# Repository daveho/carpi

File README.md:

Hardware design and code for Raspberry Pi based car entertainment device.  Everything is up and running and works fairly well at this point.  I wrote a [blog post](http://daveho.github.io/2014/04/19/carpi-car-videos-with-the-raspberry-pi.html) that summarizes the project.

The [wiki](https://github.com/daveho/carpi/wiki) has complete information on building the device and installing the software.

Everything (software and hardware) is open source: see the file
LICENSES.txt for details.

The basic idea is being able to play videos and music
from the Raspberry Pi.  The user interface consists
of a 2.2" LCD and 6 keyswitches.  A sandwich-style
enclosure consisting of two pieces of laser-cut acrylic
and various bits of hardware has been designed and assembled.
The "enclosure" directory has complete CAD drawings.

Here is a photo of the assembled device (with the Raspberry Pi,
the LCD module, and the keyswitches):

Current status of the software is

* It's a console (ncurses) app.  This probably won't change,
  although the software makes a clean separation between
  controllers and views, and the former are completely
  independent of the latter, so a proper GUI interface
  could be supported.
* The LCD display is assumed to be 240x320, accessed as
  a Linux framebuffer device with fbcons.  (Specifically,
  an SPI-based LCD using the ILI9340 controller chip,
  supported by fbtft using the "adafruit22a" driver.
  Note that the LCD I'm using isn't specifically the
  Adafruit one, but appears to be completely compatible.)
  With a 8x16 font this gives us a 30x20 text display.
* Music playing works using mpg321 and ogg123 via the
  remote control interface (actually ogg123 playback doesn't
  work, need to investigate this).
* Pushbutton input is supported using the RPi's GPIO.
* Video playing is supported by running omxplayer as a
  subprocess, with video output going to the composite output
  (because composite video monitors for cars are super cheap).

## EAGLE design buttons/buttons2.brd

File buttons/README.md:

This directory has schematics, PCB layout, and firmware for the
board that has the pushbuttons on it.  An attiny2313 or attiny4313
microcontroller does the debouncing.  This board also has a header
that connects to the LCD.

**buttons2.sch** and **buttons2.brd** are the schematic and board layout,
in Eagle CAD.

Rendering (via [OSH Park](http://www.oshpark.com), which is where I had the boards fabricated):

Note that the PCB uses Cherry MX keyboard switches.  **cherrymx.lbr** is a
(very slightly) modified version of the following Eagle library:
https://github.com/c0z3n/cherrymx-eagle

[I sent a pull request with my changes, which were purely improvements
to the schematic symbol.]

**buttons.c** is the firmware that runs on the attiny2313.
**Makefile** will compile it (using avr-gcc) and program it to the
device (using avrdude).

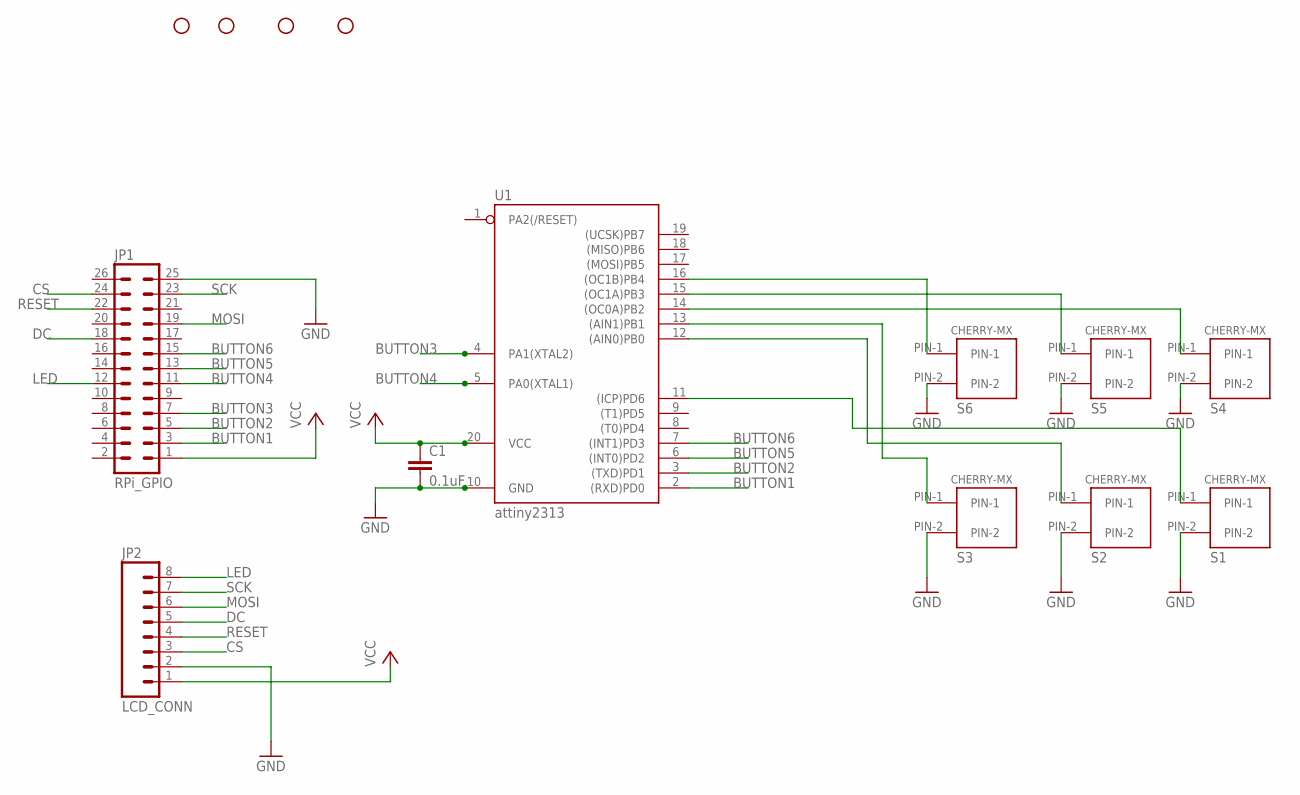
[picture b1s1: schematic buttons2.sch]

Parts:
C1: 0.1uF; C2.5-2
JP1: RPi_GPIO; ML26
JP2: LCD_CONN; 1X08
S1, S2, S3, S4, S5, S6: CHERRY-MX-I
STANDOFF1, STANDOFF2, STANDOFF3, STANDOFF4: STAND-OFF
U1: attiny2313; DIL20

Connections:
BUTTON1: JP1.3, U1.2 ((RXD)PD0)
BUTTON2: JP1.5, U1.3 ((TXD)PD1)
BUTTON3: JP1.7, U1.4 (PA1(XTAL2))
BUTTON4: JP1.11, U1.5 (PA0(XTAL1))
BUTTON5: JP1.13, U1.6 ((INT0)PD2)
BUTTON6: JP1.15, U1.7 ((INT1)PD3)
CS: JP1.24, JP2.3
DC: JP1.18, JP2.5
GND: C1.2, JP1.25, JP2.2, S1.PIN-2, S2.PIN-2, S3.PIN-2, S4.PIN-2, S5.PIN-2, S6.PIN-2, U1.10 (GND)
LED: JP1.12, JP2.8
MOSI: JP1.19, JP2.6
unnamed: S6.PIN-1, U1.16 ((OC1B)PB4)
unnamed: S5.PIN-1, U1.15 ((OC1A)PB3)
unnamed: S4.PIN-1, U1.14 ((OC0A)PB2)
unnamed: S3.PIN-1, U1.13 ((AIN1)PB1)
unnamed: S2.PIN-1, U1.12 ((AIN0)PB0)
unnamed: S1.PIN-1, U1.11 ((ICP)PD6)
RESET: JP1.22, JP2.4
SCK: JP1.23, JP2.7
VCC: C1.1, JP1.1, JP2.1, U1.20 (VCC)

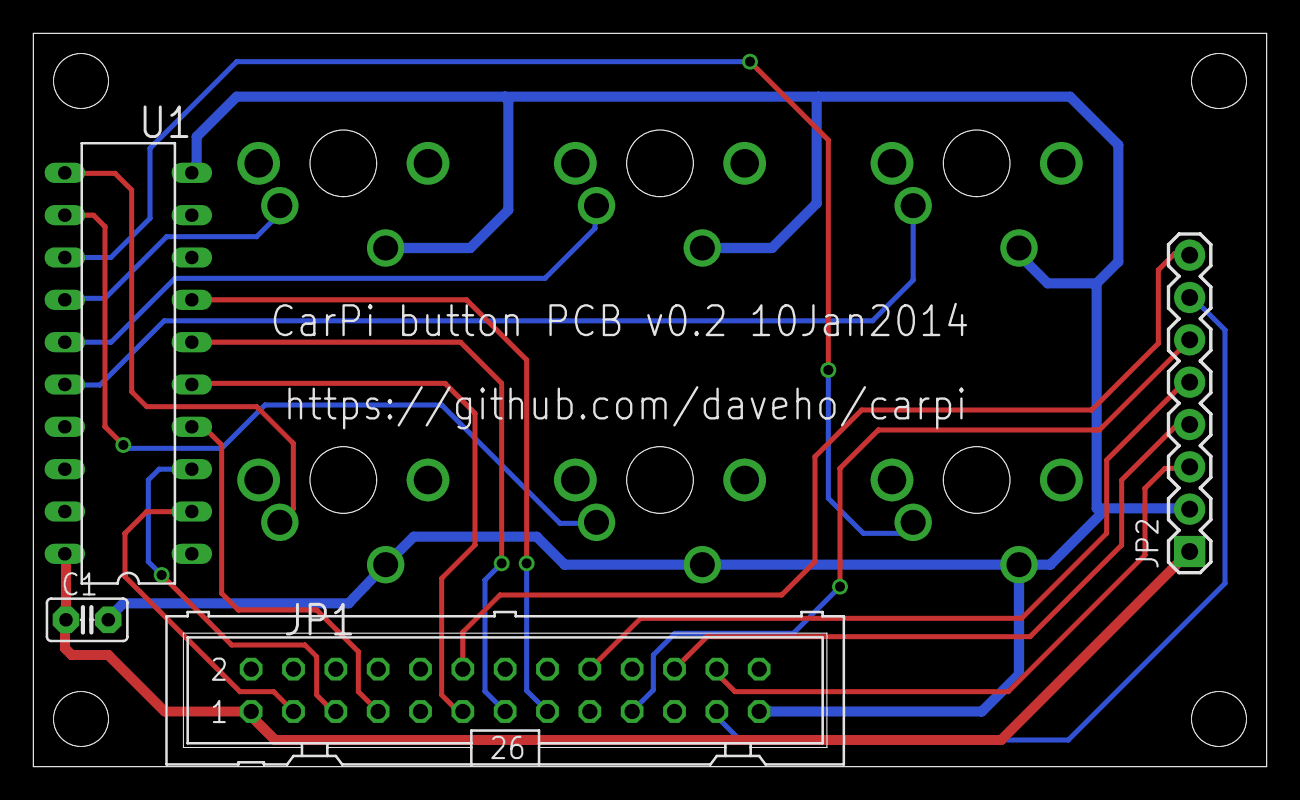
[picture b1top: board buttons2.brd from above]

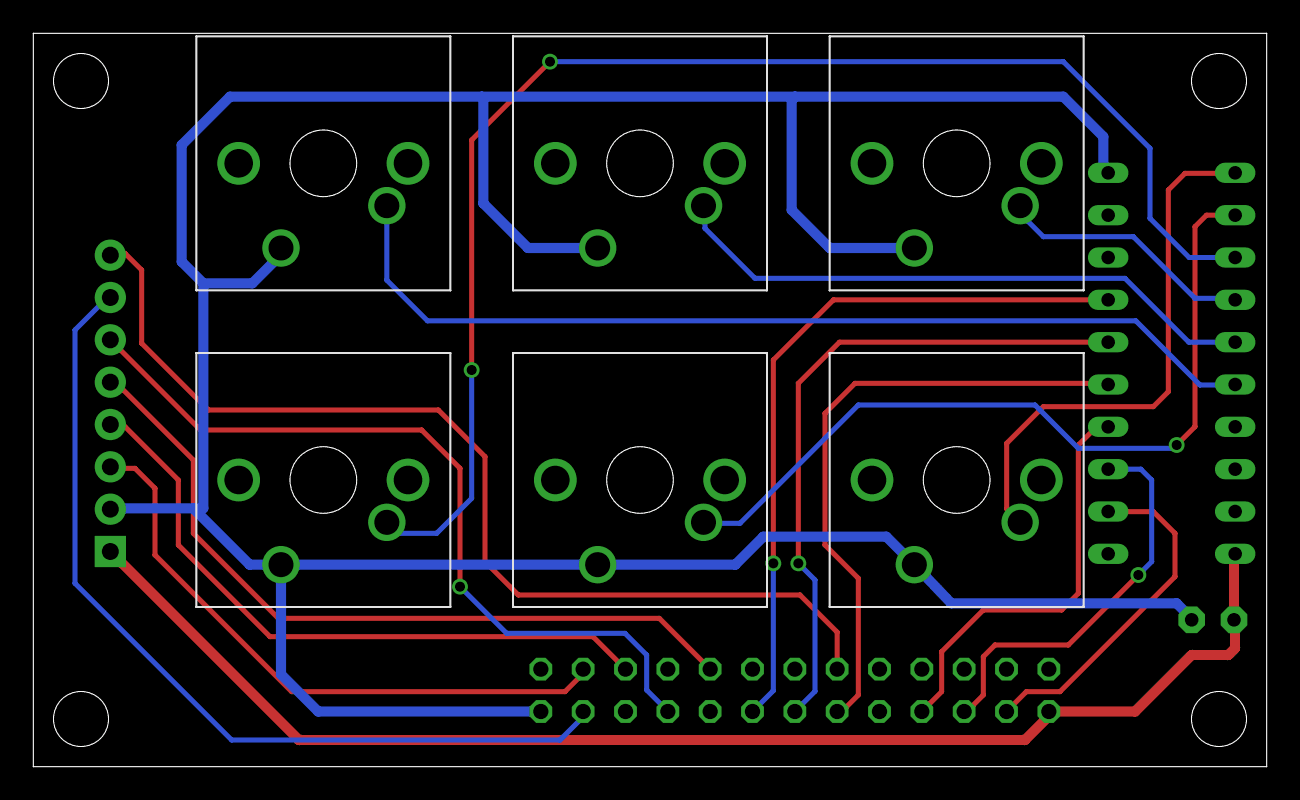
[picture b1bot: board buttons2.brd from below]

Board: 2 copper layers, 74.0 x 44.0 mm, 14 parts (6 on the bottom side), 20 nets.

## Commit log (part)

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2013-12-13 initial checkin of gtk3 tutorial code
2013-12-13 set window width and height
2013-12-13 added CarPiMainWindow object
    This serves as the top-level object for the GUI.
    Contains a GtkFixed as the main container for the
    overall UI.
2013-12-21 started log, enclosure design
2013-12-21 made it 5"x3" to allow room for board mounts
2013-12-21 rpi model B CAD drawing
2013-12-21 notes for 12/21
2013-12-22 new plate size, Rpi outline w/ ref at 0,0
2013-12-22 corrected orientation of Rpi outline
2013-12-22 good progress on enclosure design
2013-12-22 note about fixing orientation of Rpi drawing
2013-12-22 clarification about standoffs
2013-12-23 move standoffs and RPi for better clearance
    Added a layer to the drawing to show the approximate size
    of the standoffs. Was concerned that the bottom right
    standoff would block access to the ethernet port, so moved
    all of the standoffs 1mm horizontally and vertically
    towards the corners, and moved the RPi further towards
    the top. This should allow good clearance for the
2013-12-23 starting drawing of LCD
2013-12-23 basic drawing of LCD
2013-12-23 started parts list
2013-12-23 started outline of buttons protoboard
2013-12-23 more work on parts list
2013-12-23 updates for using 4x6cm board for buttons
2013-12-24 starting over with source code
2013-12-24 restart code, starting with audio player
    Created PlaySound class, for playing an audio file using
    mpg321 or ogg123 using their remote control interface.
    Using CodeLite as the C++ IDE.
2013-12-24 started Thread, Event, and EventQueue classes
    Modified PlaySound to use a Thread subclass for the
    status monitor thread.
2013-12-24 s,Foobar,CarPi,g
2013-12-25 code cleanup
2013-12-25 added MenuController; made ConsMenuView read-only
    From now on, ALL of the views will be read-only, and
    this will be enforced through having model object pointer
    be to a const object.
    This should work really well: since we have our
    own event system, the views have no obligation to
    handle user input events, and in fact do not even
2013-12-25 start support for menu scrolling
2013-12-25 scrolling works!
2013-12-26 started main menu
    There will be one menu class and one menu controller class
    per menu. Seems to be workable. The controller will
    "own" the menu, and thus be responsible for cleaning it
    up when the controller and view are no longer needed.
2013-12-26 made Menu abstract; added StaticMenu
2013-12-26 created CarPiApp main class; started file nav
2013-12-26 set MenuItem ptr in SELECTION_CHANGED events
2013-12-26 directory navigation mostly works!
2013-12-26 only include .mp3 and .ogg files in music nav
2013-12-26 added left (back) button support for file nav
2013-12-27 adjusted for larger diameter standoffs
2013-12-27 make getState a const method
2013-12-27 playing single music files works!
    There is a lot that needs to be improved, but basically it
    works.
2013-12-28 display ID3 information
2013-12-28 fix bugs in id3 parsing
2013-12-29 minor cleanups
2013-12-29 add trailing "/" to directory names in file nav
2013-12-29 refactoring to support multi-file playback
2013-12-29 more refactoring for multi-file playback
2013-12-29 more accurate tracking of player status
2013-12-29 nicer looking music player view
2013-12-29 stop current song before switching
2013-12-31 display current track / number of tracks
2013-12-31 start refactoring to break controller->view dep
    CarPiApp will now be subclassed to create views as
    necessary.
2013-12-31 #include cleanup
2013-12-31 added copyright header
2013-12-31 added readme
2013-12-31 fixed bug in PlaySound - works with ogg123 now
    We weren't sending a newline after the initial load
    command. Not sure how it ever worked at all with mpg321.
    Also, ogg123 doesn't report file metadata (title, artist,
    and album), so just report the filename.
2013-12-31 attempted fix for ogg123 failing to send @P msgs
    ogg123 doesn't send a @P message when the current file
    has finished playing, meaning that we don't know to
    start the next file playing. Attempt to work around
    by generating a status callback at the appropriate time.
    Doesn't actually work - investigating.
2014-01-01 log update
2014-01-02 allow programming of AVR button debounce firmware
2014-01-02 blink LED on PD4 for debugging
    Also, stick with default 1 MHz internal oscillator - I bricked
    one of my attiny2313 trying to configure the fuses for 128 KHz
    internal oscillator. Button press detection doesn't seem to
    work, but blinking LED does work.
2014-01-02 pass-through without debouncing works
    Clearly there is something wrong with the debouncing
    code, but the circuit works fine. I may send the board
    off to be manufactured!
2014-01-02 debouncing code works perfectly!
    I was shifting the mask bit twice per loop iteration.
    Changed Makefile so that debugging (the heartbeat LED blink
    on PD4) is disabled by default.
2014-01-03 placed buttons in wrong order on PCB
    I laid out the buttons in exactly the opposite order
    on the PCB, so I needed to change the firmware to
    compensate. Not a big deal.
2014-01-03 adjust standoff positions
    Each standoff is exactly 2.84mm V/H from the board edges.
2014-01-03 larger board (keep standoffs from cutout)
2014-01-03 added updated outline for button board
2014-01-03 top and bottom plates!
2014-01-04 added 1"x1" reference square
2014-01-04 enclosure CAD drawings are complete
2014-01-04 readme/license information
2014-01-04 bugfix in StringUtil::padWithSpaces
    wasn't properly handling the case where the string
    was greater than the desired field width
2014-01-04 update copyright year
2014-01-04 start video player (untested)
2014-01-05 code cleanups
2014-01-05 more reasonable debug LED blink rate
2014-01-05 another tweak to debug LED blink
2014-01-06 set DEBUG=false
2014-01-06 work around RPi booting in safe mode
2014-01-06 output button signals as 0=pressed
    This avoids accidentally causing the RPi to boot in
    safe mode, which happens if SCL (GPIO 3) is held low on
    boot.
2014-01-06 fixed comment
2014-01-06 note about pushbutton interfacing
2014-01-07 added Raspberry Pi makefile
2014-01-07 remove CarPi.mk: it's only useful with CodeLite
2014-01-08 experiment to use Cherry MX keyboard switches
2014-01-08 I think I have a workable Cherry MX design
2014-01-09 rip up traces to buttons, move attiny2313
    Buttons need to be mirrored because they will be
    on the bottom of the board.
    The attiny2313 was too close to the top left standoff.
2014-01-09 mirrored buttons
2014-01-09 routed all signals
2014-01-09 more or less complete PCB for Cherry MX switches
2014-01-09 moved buttons: keycaps are 18mm x 18mm
    I think everything will still fit, but unfortunately
    everything must be routed again...
2014-01-09 some minor routing tweaks
2014-01-09 move power trace away from standoff
2014-01-10 allow 19mm H/V between switch centers
    The keycaps are 18mm x 18mm, so hopefull this is enough
    room.
2014-01-10 various layout tweaks, improved clearances, etc.
2014-01-10 more routing tweaks
2014-01-10 updated buttons2/plate drawing for 19mm keycap
    Made the PCB 74mm rather than 73mm to allow more space
    between button cutout and button PCB screw hole.
2014-01-10 eliminated an unnecessary via
2014-01-10 move URL away from via
    Vias are plated, I guess, so would interrupt the
    silkscreen layer.
2014-01-12 first attempt at GPIO read support
    I don't think we need wiringPi: the basic user-mode
    GPIO access provided by Linux should be sufficient.
    It allows blocking select/poll if the underlying GPIO
    hardware supports interrupts.
2014-01-12 script to unexport GPIO pins
2014-01-12 various improvements to GPIO support
    Don't explicitly set the pin direction, just verify
    that it's "in".
    Some work on setting the edge (untested).
2014-01-12 reading GPIO pins (using interupts) works!!!
    The test program uses select to wait for a pin
    interrupt (on any pin) to occur, then prints outs
    the values of all pins. Seems to work!
2014-01-12 made GpioPin::getValue const
    Also, verified that all pins are read correctly
    (they are)!
2014-01-12 button input reader thread (untested)
    This is enabled only when compiling on the RPi.
2014-01-12 pushbutton input is working
2014-01-16 only do GPIO test if RASPBERRY_PI defined
2014-01-17 update log
2014-01-17 update - button PCB v0.1 works
2014-01-18 use attiny4313
2014-01-18 make corners less round, boardmount screw holes
2014-01-18 bottom plate (new design with Cherry MX switches)
    The bottom plate just has holes for corner (plate)
    standoffs, board mounts, and RPi mounting hole standoffs.
2014-01-18 top plate (new design for Cherry MX switches)
    This has the corner standoff screw holes, LCD screw
    holes, button PCB screw holes, and the rectangular
    cutout for the keyswitches/keycaps.
2014-01-18 made side-by-side rather than on top of each other
    My thought is that this is easier to replicate multiple
    copies of.
2014-01-18 submitted request for laser cutting quote
    This is for the new design with the Cherry MX
    keyswitches/keycaps.
2014-01-19 working on support for playing video
    Doesn't work yet, but reaches the point where it
    *should* start playing video :-)
2014-01-19 update log (close to playing video)
2014-01-25 working on splitting long strings into lines
    Doesn't quite seem to work when used in the music
    player view - need to figure out.
2014-01-26 allow exiting the video player using left btn
    If the video is playing, the left button is
    ignored. The idea is to prevent accidental
    stoppages that might upset the viewers :-)
2014-01-28 added pictures of completed enclosure
2014-01-28 added README.md for old enclosure design
2014-01-28 github doesn't allow style attributes
2014-01-28 s,drawing,photo,
2014-02-02 update log and readme
2014-02-04 build ButtonDaemon by default
    Also, fixed a bug (initial button state was being set
    to pressed rather than released). And, added a debug
    printf so we can see when button events are generated.
    ButtonDaemon sort of works: however, key events only
    seem to appear every 4 presses. Seems to be some kind
    of buffering issue.
2014-02-08 trying to debug generation of uinput key events
    I am going to abandon this branch - I really don't
    understand how uinput works. The current behavior is
    that key events aren't received by fbcons until 8 of
    them (4 presses and 4 releases) have been generated,
    which is not a useful behavior.
    Instead, I'm going to use the UNBLANKSCREEN ioctl
2014-02-08 force screen unblank on button press
    It turns out that there is an ioctl that forces screen
    unblanking - we don't need to mess around with uinput
    after all.
2014-02-08 success with Philips DVD slave screen
2014-02-09 renderings of PCB
2014-02-12 update log (wiring for car!)
2014-02-12 Add install target, allow system shutdown
2014-02-13 correct note about inittab
2014-02-13 note about trying TIOCL_SETVESABLANK
2014-02-14 got uinput events to work!!!
    The trick was to send an EV_SYN event after the key events,
    which apparently forces the events to be pushed to
    the consumer (in our case, the console).
2014-02-14 translate button events to key events using uinput
2014-02-15 progress on improving backlight situation
2014-02-15 confirmed that LCD backlight issue is fixed
2014-02-16 s,enclosure,device,
2014-03-02 bugfix with seek handling
    I'd forgotten to set EventHandler::HANDLED for up and
    down button presses, and to set m_rightPressed back to
    false.
2014-03-02 button event daemon is not needed
2014-03-02 updates (car audio!)
2014-03-02 fixed return value of seek method
2014-03-04 working on playback settings
2014-03-05 get rid of CodeLite project
    Also, renamed Makefile.pi as just Makefile.
2014-03-05 fix missing break statement
2014-03-05 eliminated StaticMenu class: Menu is now concrete
    In general menus should not have behavior other than
    maintaining a list of items, so subclasses are
    unnecessary.
2014-03-05 add copyright headers
2014-04-21 update wiki since project is basically finished
2015-06-26 allow switching between composite and HDMI output
2017-07-05 started code to monitor omxplayer output

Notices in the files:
parts and their libraries:
SparkFun-Electromechanical: Licensing: CC v3.0 Share-Alike You are welcome to use this library for commercial purposes.
